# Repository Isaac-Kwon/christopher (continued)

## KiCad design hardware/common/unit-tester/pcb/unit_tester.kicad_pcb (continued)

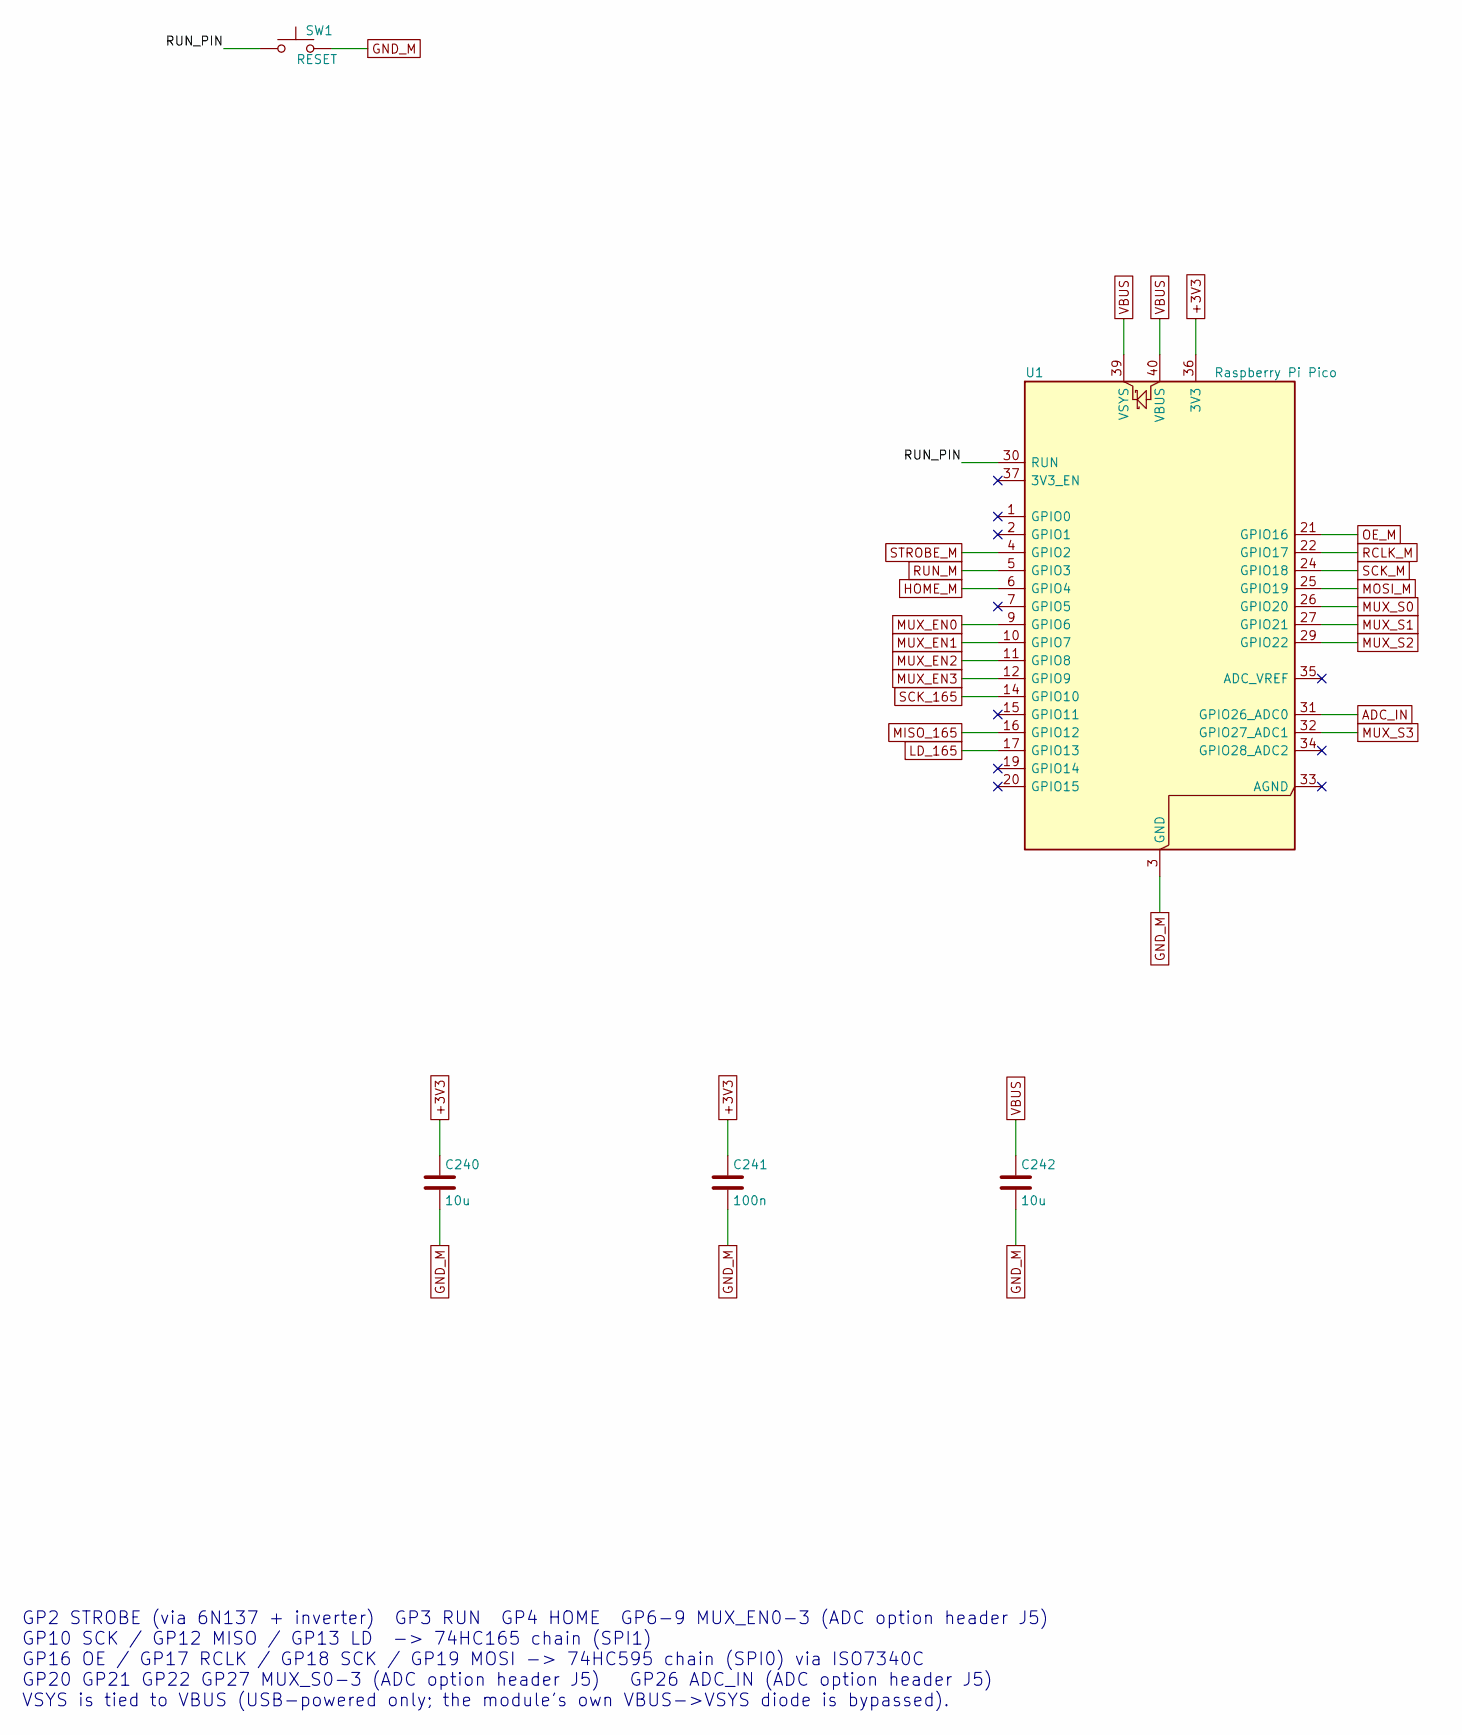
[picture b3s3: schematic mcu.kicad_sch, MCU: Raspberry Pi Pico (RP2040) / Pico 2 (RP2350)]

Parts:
C240, C242: 10u; C_0805_2012Metric
C241: 100n; C_0603_1608Metric
SW1: RESET; SW_SPST_PTS645Sx43SMTR92
U1: Raspberry Pi Pico; RaspberryPi_Pico_Common_THT

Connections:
+3V3: C240.1, C241.1, U1.36 (3V3); also elsewhere on the board
/MCU/RUN_PIN: SW1.1, U1.30 (RUN)
ADC_IN: U1.31 (GPIO26_ADC0); also elsewhere on the board
GND_M: C240.2, C241.2, C242.2, SW1.2, U1.3 (GND), U1.8 (GND), U1.13 (GND), U1.18 (GND), U1.23 (GND), U1.28 (GND), U1.38 (GND); also elsewhere on the board
HOME_M: U1.6 (GPIO4); also elsewhere on the board
LD_165: U1.17 (GPIO13); also elsewhere on the board
MISO_165: U1.16 (GPIO12); also elsewhere on the board
MOSI_M: U1.25 (GPIO19); also elsewhere on the board
MUX_EN0: U1.9 (GPIO6); also elsewhere on the board
MUX_EN1: U1.10 (GPIO7); also elsewhere on the board
MUX_EN2: U1.11 (GPIO8); also elsewhere on the board
MUX_EN3: U1.12 (GPIO9); also elsewhere on the board
MUX_S0: U1.26 (GPIO20); also elsewhere on the board
MUX_S1: U1.27 (GPIO21); also elsewhere on the board
MUX_S2: U1.29 (GPIO22); also elsewhere on the board
MUX_S3: U1.32 (GPIO27_ADC1); also elsewhere on the board
OE_M: U1.21 (GPIO16); also elsewhere on the board
RCLK_M: U1.22 (GPIO17); also elsewhere on the board
RUN_M: U1.5 (GPIO3); also elsewhere on the board
SCK_165: U1.14 (GPIO10); also elsewhere on the board
SCK_M: U1.24 (GPIO18); also elsewhere on the board
STROBE_M: U1.4 (GPIO2); also elsewhere on the board
VBUS: C242.1, U1.39 (VSYS), U1.40 (VBUS)

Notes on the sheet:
GP2 STROBE (via 6N137 + inverter) GP3 RUN GP4 HOME GP6-9 MUX_EN0-3 (ADC option header J5) GP10 SCK / GP12 MISO / GP13 LD -> 74HC165 chain (SPI1) GP16 OE / GP17 RCLK / GP18 SCK / GP19 MOSI -> 74HC595 chain (SPI0) via ISO7340C GP20 GP21 GP22 GP27 MUX_S0-3 (ADC option header J5) GP26 ADC_IN (ADC optio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

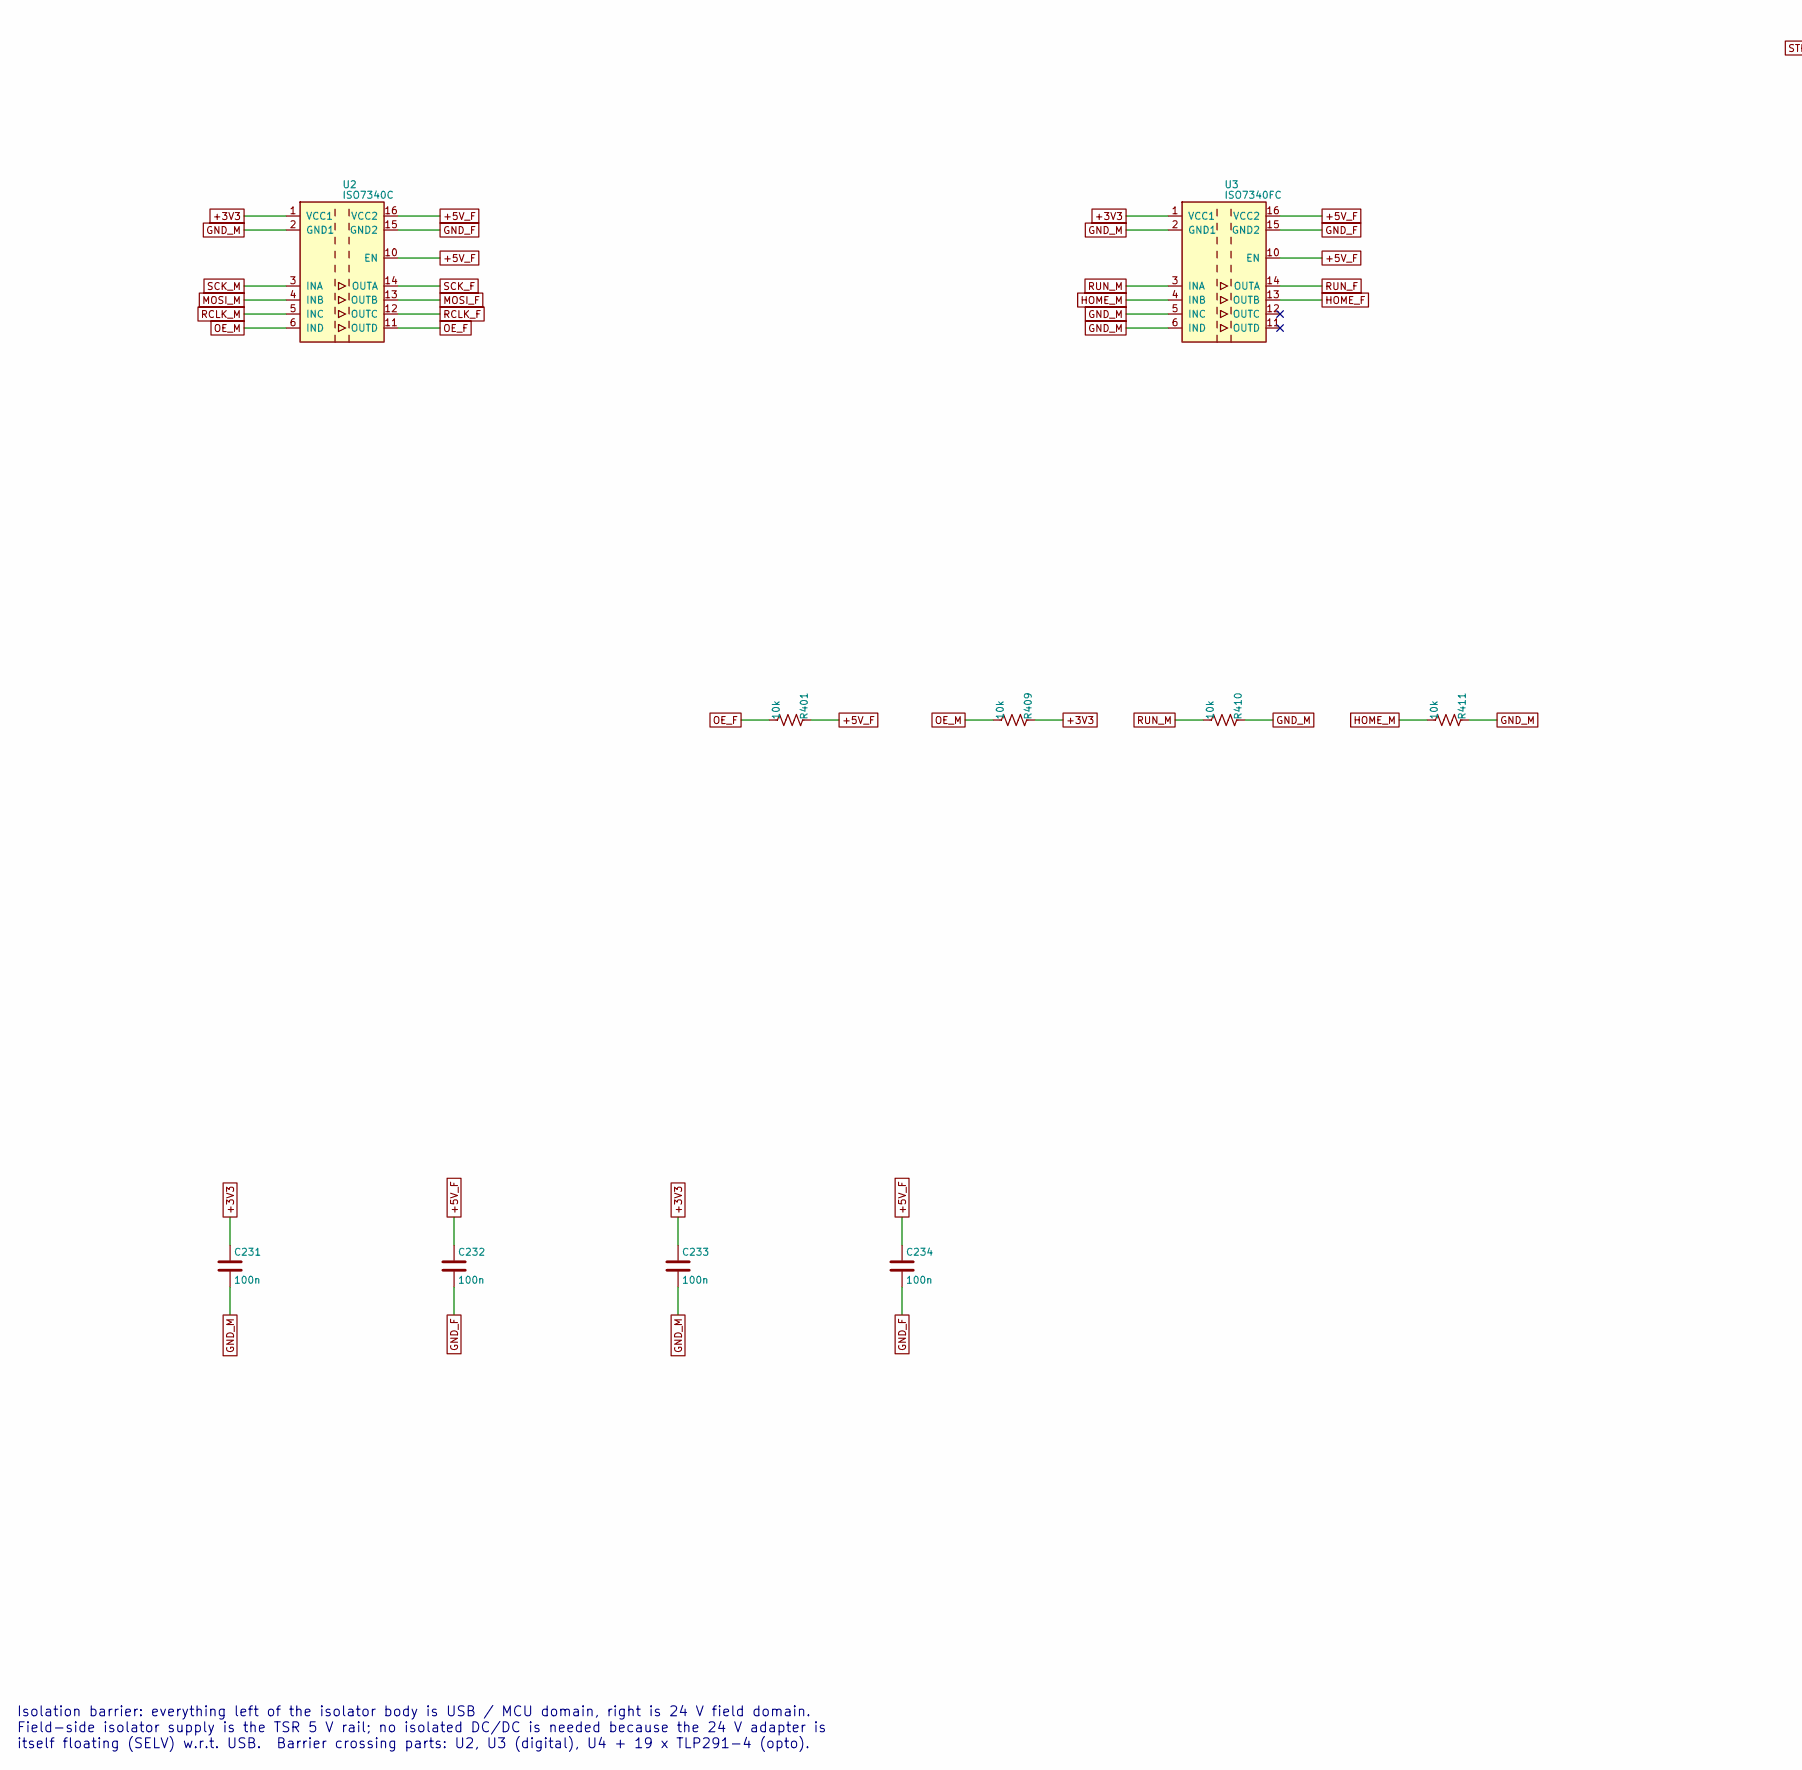
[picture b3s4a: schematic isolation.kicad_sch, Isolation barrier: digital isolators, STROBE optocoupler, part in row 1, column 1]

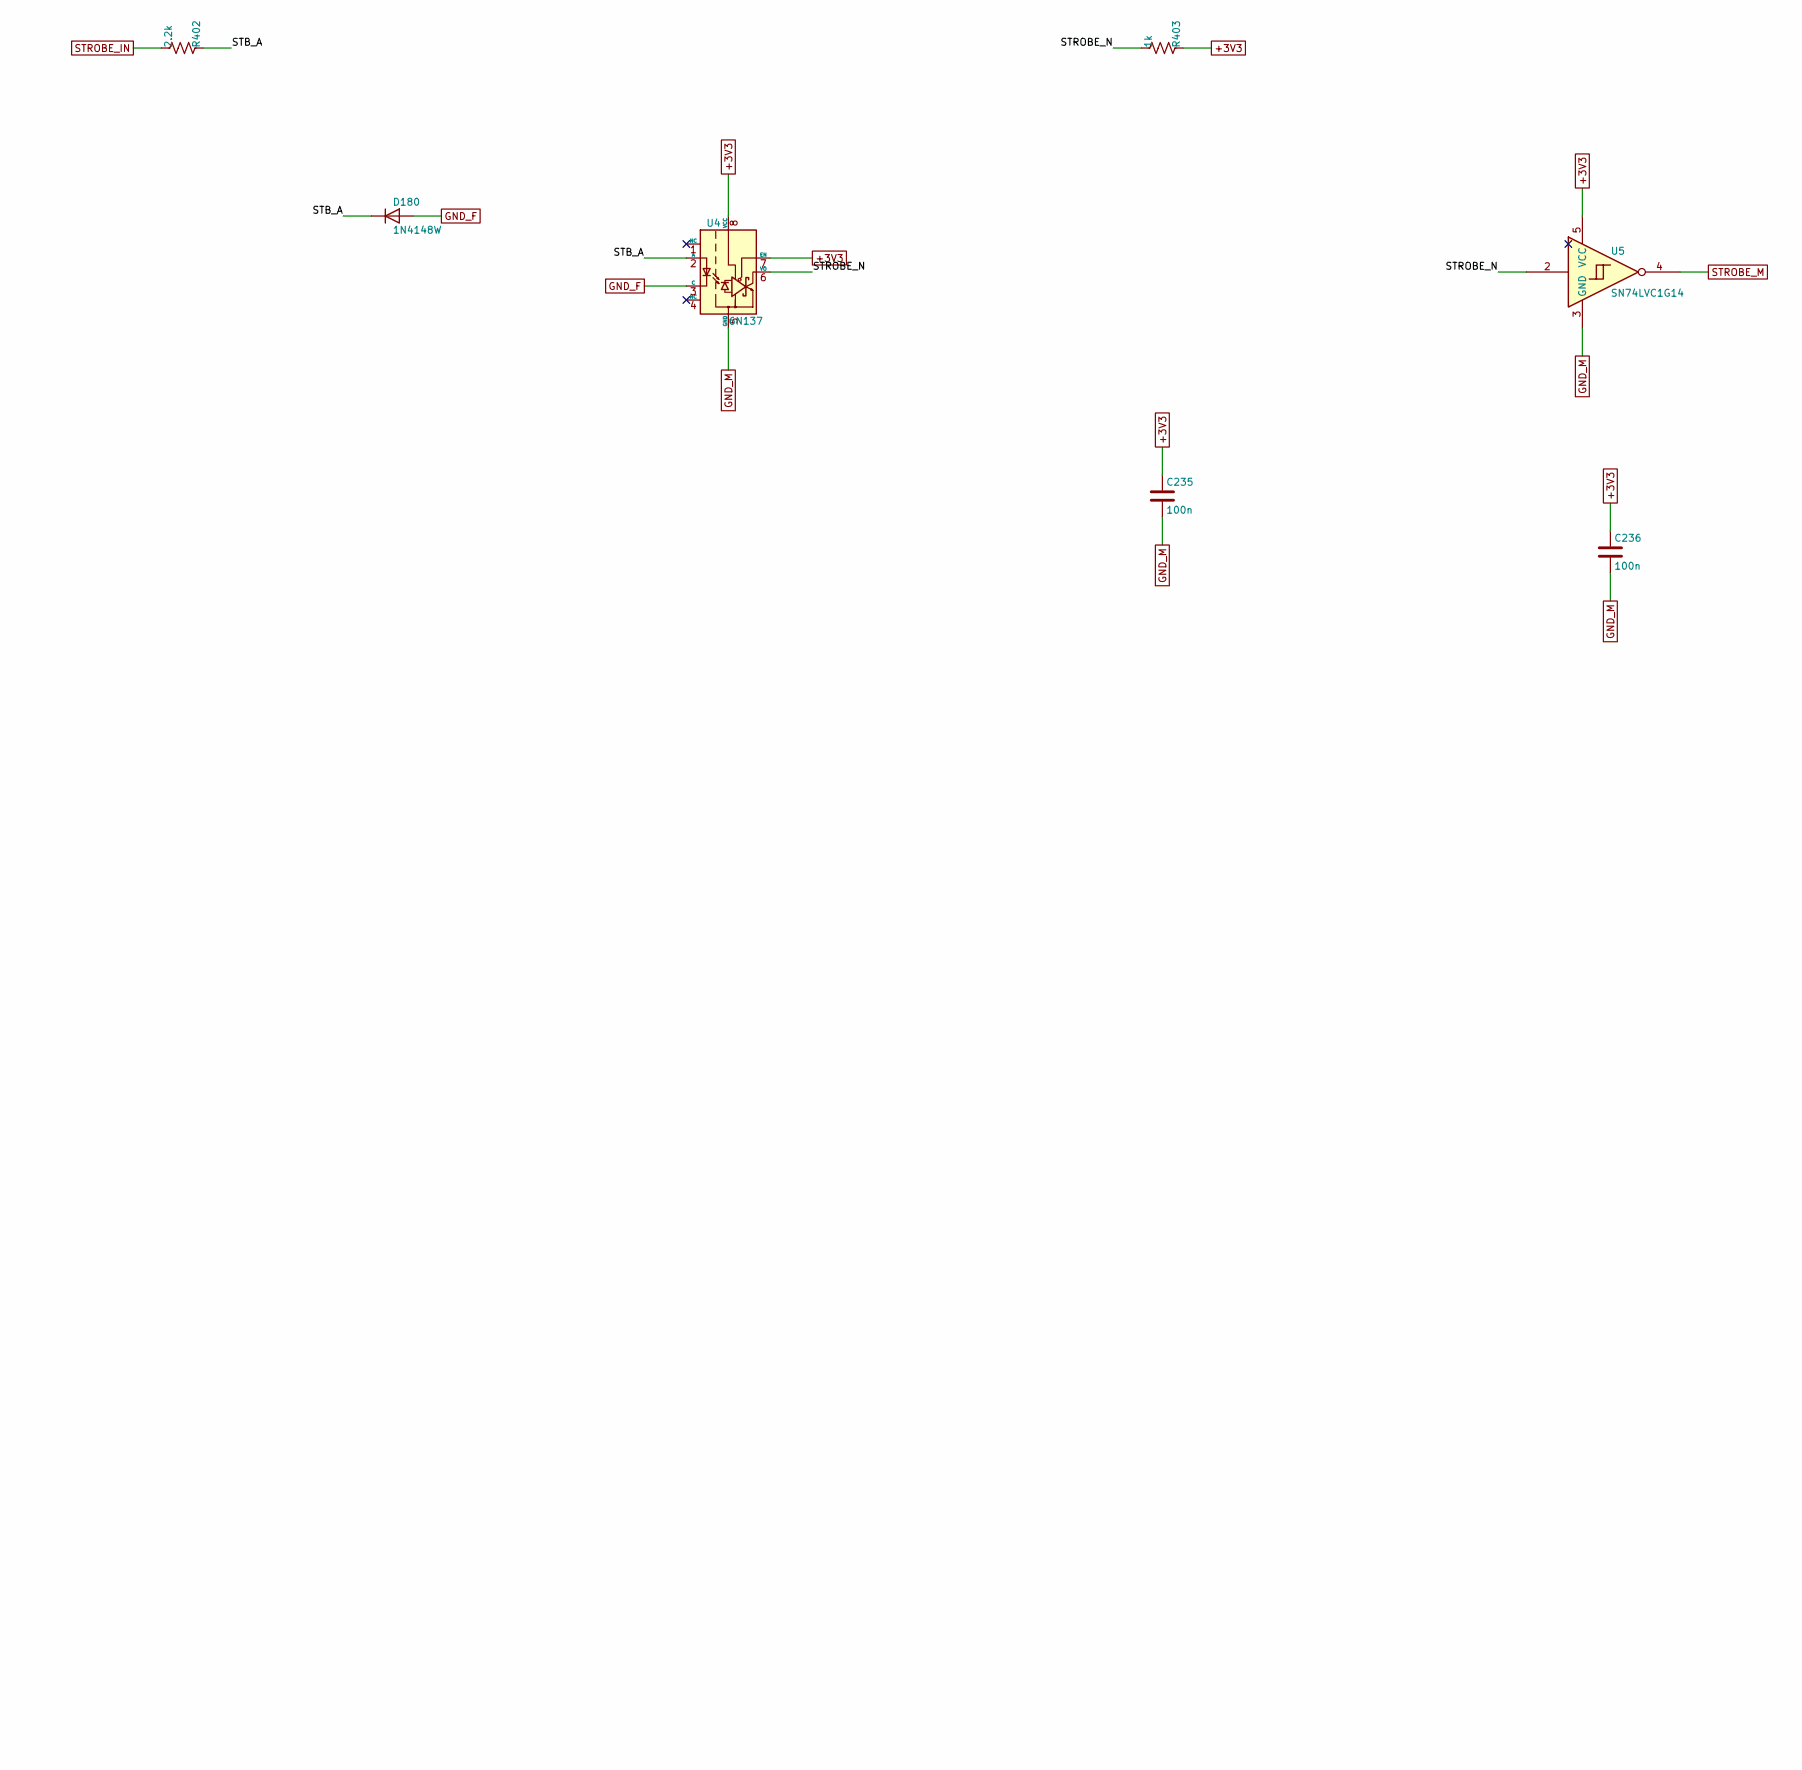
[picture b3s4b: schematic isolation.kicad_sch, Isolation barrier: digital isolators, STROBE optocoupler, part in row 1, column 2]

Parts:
C231, C232, C233, C234, C235, C236: 100n; C_0603_1608Metric
D180: 1N4148W; D_SOD-123
R401, R409, R410, R411: 10k; R_0603_1608Metric
R402: 2.2k; R_0603_1608Metric
R403: 1k; R_0603_1608Metric
U2: ISO7340C; SOIC-16W_7.5x10.3mm_P1.27mm
U3: ISO7340FC; SOIC-16W_7.5x10.3mm_P1.27mm
U4: 6N137; DIP-8_W7.62mm
U5: SN74LVC1G14; SOT-23-5

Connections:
+3V3: C231.1, C233.1, C235.1, C236.1, R403.2, R409.2, U2.1 (VCC1), U3.1 (VCC1), U4.7 (EN), U4.8 (VCC), U5.5 (VCC); also elsewhere on the board
+5V_F: C232.1, C234.1, R401.2, U2.10 (EN), U2.16 (VCC2), U3.10 (EN), U3.16 (VCC2); also elsewhere on the board
/ISOLATION/STB_A: D180.1 (K), R402.2, U4.2 (A)
/ISOLATION/STROBE_N: R403.1, U4.6 (VO), U5.2
GND_F: C232.2, C234.2, D180.2 (A), U2.9 (GND2), U2.15 (GND2), U3.9 (GND2), U3.15 (GND2), U4.3 (C); also elsewhere on the board
GND_M: C231.2, C233.2, C235.2, C236.2, R410.2, R411.2, U2.2 (GND1), U2.8 (GND1), U3.2 (GND1), U3.5 (INC), U3.6 (IND), U3.8 (GND1), U4.5 (GND), U5.3 (GND); also elsewhere on the board
HOME_F: U3.13 (OUTB); also elsewhere on the board
HOME_M: R411.1, U3.4 (INB); also elsewhere on the board
MOSI_F: U2.13 (OUTB); also elsewhere on the board
MOSI_M: U2.4 (INB); also elsewhere on the board
OE_F: R401.1, U2.11 (OUTD); also elsewhere on the board
OE_M: R409.1, U2.6 (IND); also elsewhere on the board
RCLK_F: U2.12 (OUTC); also elsewhere on the board
RCLK_M: U2.5 (INC); also elsewhere on the board
RUN_F: U3.14 (OUTA); also elsewhere on the board
RUN_M: R410.1, U3.3 (INA); also elsewhere on the board
SCK_F: U2.14 (OUTA); also elsewhere on the board
SCK_M: U2.3 (INA); also elsewhere on the board
STROBE_IN: R402.1; also elsewhere on the board
STROBE_M: U5.4; also elsewhere on the board

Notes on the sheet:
Isolation barrier: everything left of the isolator body is USB / MCU domain, right is 24 V field domain. Field-side isolator supply is the TSR 5 V rail; no isolated DC/DC is needed because the 24 V adapter is itself floating (SELV) w.r.t. USB. Barrier crossing parts: U2, U3 (digital), U4 + 19 x TLP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

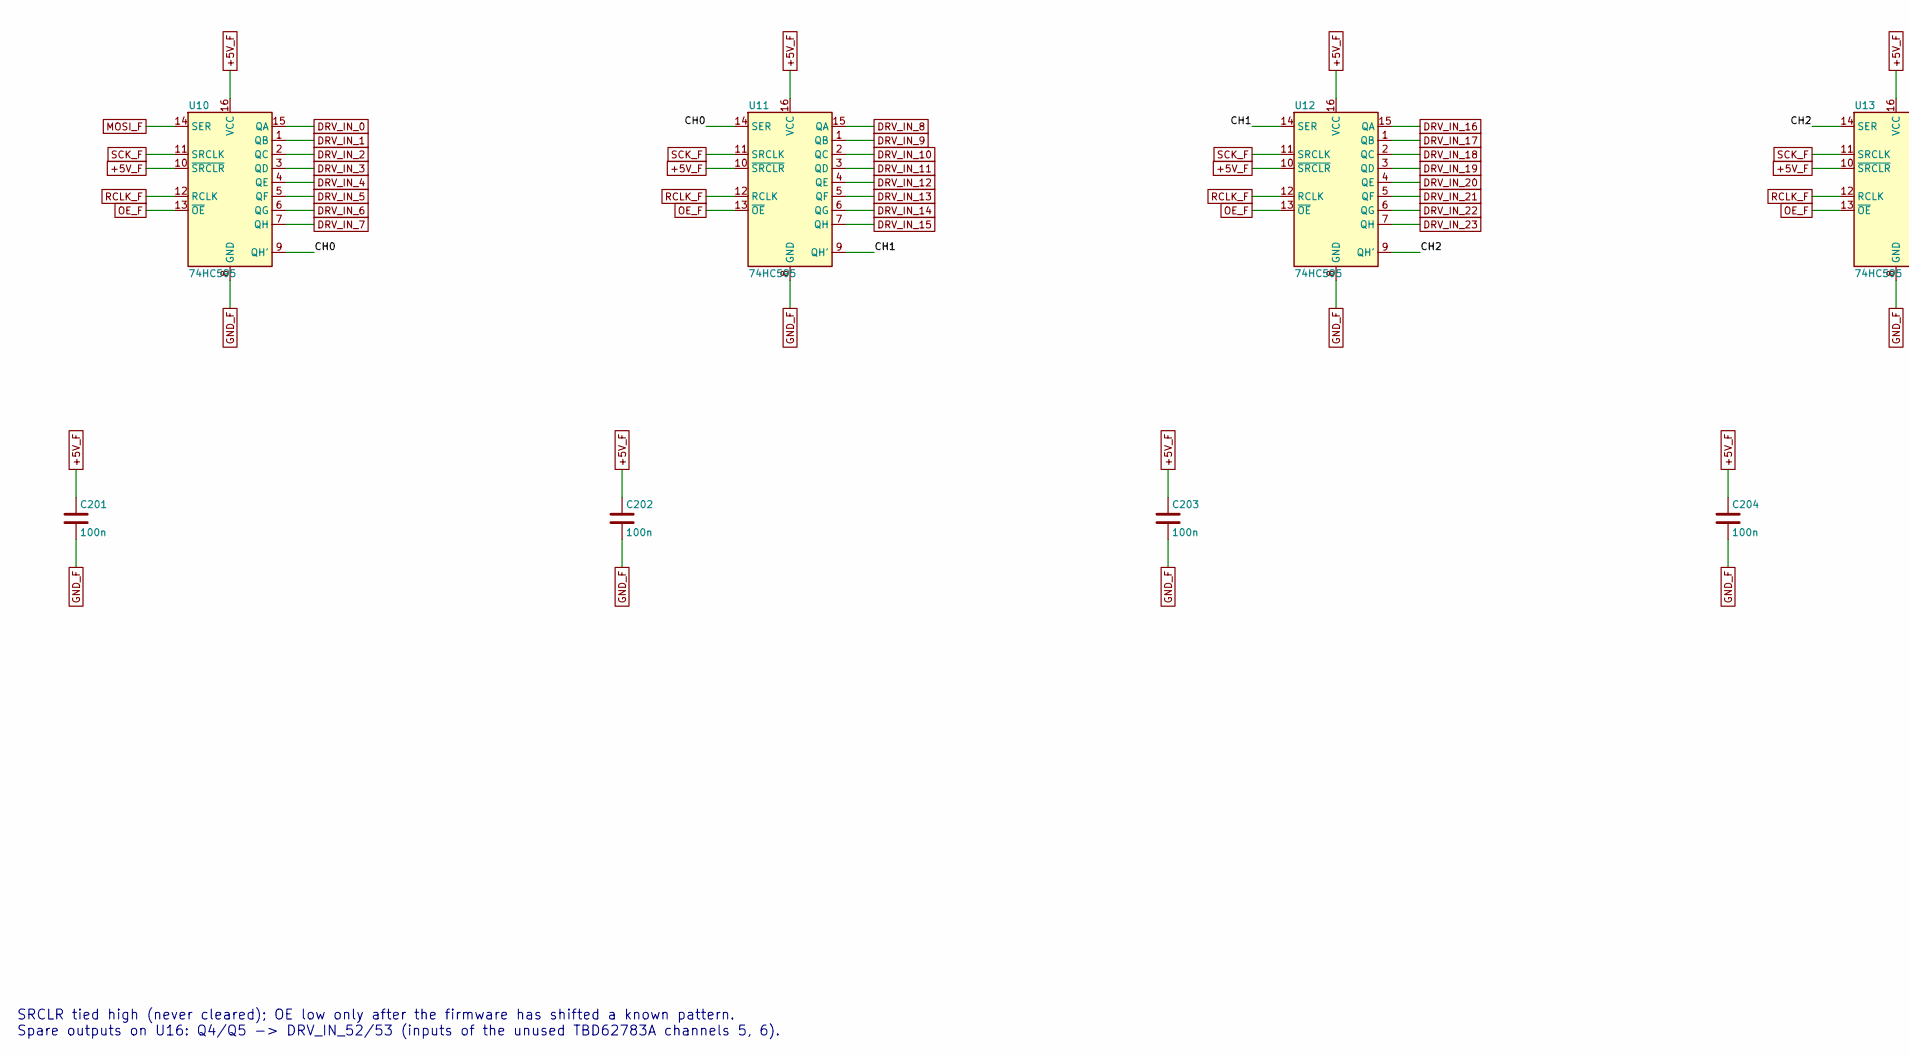
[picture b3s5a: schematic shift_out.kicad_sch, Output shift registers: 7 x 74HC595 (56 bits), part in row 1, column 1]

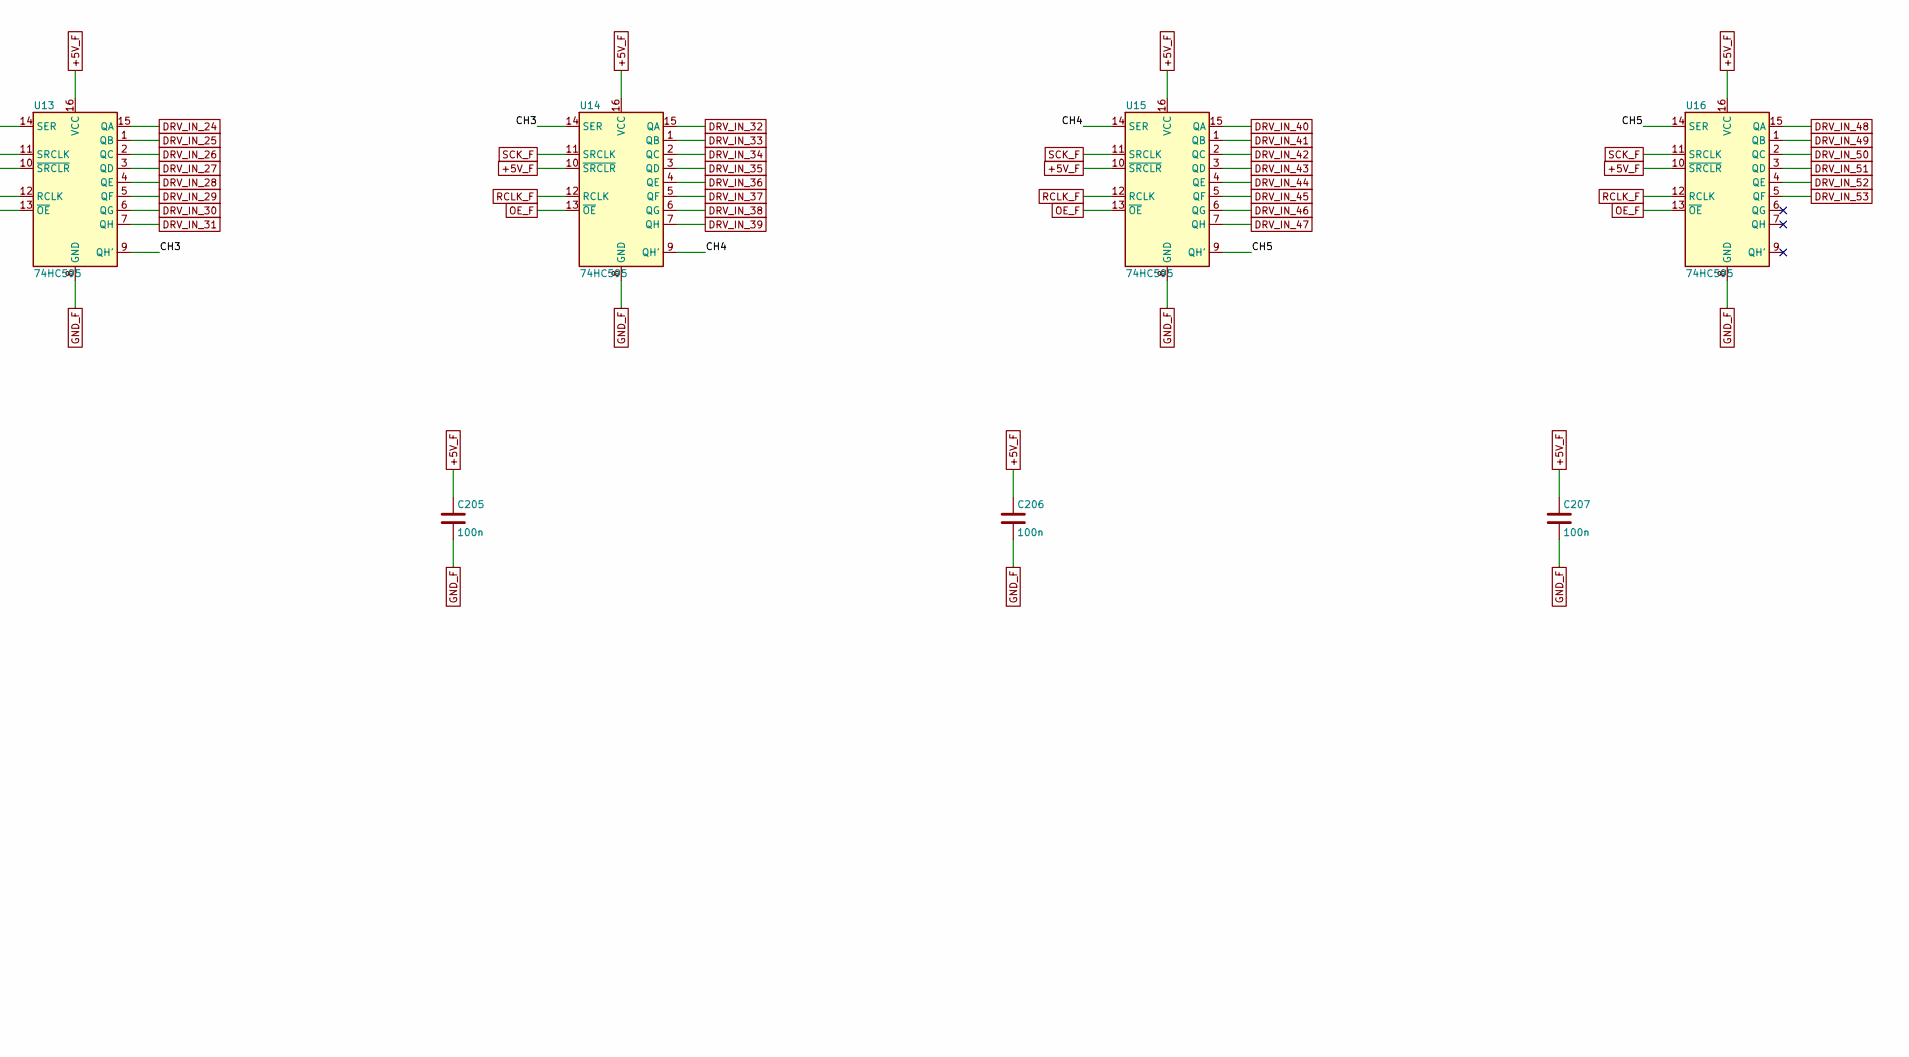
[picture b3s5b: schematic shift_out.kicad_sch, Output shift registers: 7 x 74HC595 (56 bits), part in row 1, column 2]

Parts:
C201, C202, C203, C204, C205, C206, C207: 100n; C_0603_1608Metric
U10, U11, U12, U13, U14, U15, U16: 74HC595; SOIC-16_3.9x9.9mm_P1.27mm

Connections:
+5V_F: C201.1, C202.1, C203.1, C204.1, C205.1, C206.1, C207.1, U10.10 (~SRCLR), U10.16 (VCC), U11.10 (~SRCLR), U11.16 (VCC), U12.10 (~SRCLR), U12.16 (VCC), U13.10 (~SRCLR), U13.16 (VCC), U14.10 (~SRCLR), U14.16 (VCC), U15.10 (~SRCLR), U15.16 (VCC), U16.10 (~SRCLR), U16.16 (VCC); also elsewhere on the board
/SHIFT_OUT/CH0: U10.9 (QH'), U11.14 (SER)
/SHIFT_OUT/CH1: U11.9 (QH'), U12.14 (SER)
/SHIFT_OUT/CH2: U12.9 (QH'), U13.14 (SER)
/SHIFT_OUT/CH3: U13.9 (QH'), U14.14 (SER)
/SHIFT_OUT/CH4: U14.9 (QH'), U15.14 (SER)
/SHIFT_OUT/CH5: U15.9 (QH'), U16.14 (SER)
DRV_IN_0: U10.15 (QA); also elsewhere on the board
DRV_IN_1: U10.1 (QB); also elsewhere on the board
DRV_IN_2: U10.2 (QC); also elsewhere on the board
DRV_IN_3: U10.3 (QD); also elsewhere on the board
DRV_IN_4: U10.4 (QE); also elsewhere on the board
DRV_IN_5: U10.5 (QF); also elsewhere on the board
DRV_IN_6: U10.6 (QG); also elsewhere on the board
DRV_IN_7: U10.7 (QH); also elsewhere on the board
DRV_IN_8: U11.15 (QA); also elsewhere on the board
DRV_IN_9: U11.1 (QB); also elsewhere on the board
DRV_IN_10: U11.2 (QC); also elsewhere on the board
DRV_IN_11: U11.3 (QD); also elsewhere on the board
DRV_IN_12: U11.4 (QE); also elsewhere on the board
DRV_IN_13: U11.5 (QF); also elsewhere on the board
DRV_IN_14: U11.6 (QG); also elsewhere on the board
DRV_IN_15: U11.7 (QH); also elsewhere on the board
DRV_IN_16: U12.15 (QA); also elsewhere on the board
DRV_IN_17: U12.1 (QB); also elsewhere on the board
DRV_IN_18: U12.2 (QC); also elsewhere on the board
DRV_IN_19: U12.3 (QD); also elsewhere on the board
DRV_IN_20: U12.4 (QE); also elsewhere on the board
DRV_IN_21: U12.5 (QF); also elsewhere on the board
DRV_IN_22: U12.6 (QG); also elsewhere on the board
DRV_IN_23: U12.7 (QH); also elsewhere on the board
DRV_IN_24: U13.15 (QA); also elsewhere on the board
DRV_IN_25: U13.1 (QB); also elsewhere on the board
DRV_IN_26: U13.2 (QC); also elsewhere on the board
DRV_IN_27: U13.3 (QD); also elsewhere on the board
DRV_IN_28: U13.4 (QE); also elsewhere on the board
DRV_IN_29: U13.5 (QF); also elsewhere on the board
DRV_IN_30: U13.6 (QG); also elsewhere on the board
DRV_IN_31: U13.7 (QH); also elsewhere on the board
DRV_IN_32: U14.15 (QA); also elsewhere on the board
DRV_IN_33: U14.1 (QB); also elsewhere on the board
DRV_IN_34: U14.2 (QC); also elsewhere on the board
DRV_IN_35: U14.3 (QD); also elsewhere on the board
DRV_IN_36: U14.4 (QE); also elsewhere on the board
DRV_IN_37: U14.5 (QF); also elsewhere on the board
DRV_IN_38: U14.6 (QG); also elsewhere on the board
DRV_IN_39: U14.7 (QH); also elsewhere on the board
DRV_IN_40: U15.15 (QA); also elsewhere on the board
DRV_IN_41: U15.1 (QB); also elsewhere on the board
DRV_IN_42: U15.2 (QC); also elsewhere on the board
DRV_IN_43: U15.3 (QD); also elsewhere on the board
DRV_IN_44: U15.4 (QE); also elsewhere on the board
DRV_IN_45: U15.5 (QF); also elsewhere on the board
DRV_IN_46: U15.6 (QG); also elsewhere on the board
DRV_IN_47: U15.7 (QH); also elsewhere on the board
DRV_IN_48: U16.15 (QA); also elsewhere on the board
DRV_IN_49: U16.1 (QB); also elsewhere on the board
DRV_IN_50: U16.2 (QC); also elsewhere on the board
DRV_IN_51: U16.3 (QD); also elsewhere on the board
DRV_IN_52: U16.4 (QE); also elsewhere on the board
DRV_IN_53: U16.5 (QF); also elsewhere on the board
GND_F: C201.2, C202.2, C203.2, C204.2, C205.2, C206.2, C207.2, U10.8 (GND), U11.8 (GND), U12.8 (GND), U13.8 (GND), U14.8 (GND), U15.8 (GND), U16.8 (GND); also elsewhere on the board
MOSI_F: U10.14 (SER); also elsewhere on the board
OE_F: U10.13 (~OE), U11.13 (~OE), U12.13 (~OE), U13.13 (~OE), U14.13 (~OE), U15.13 (~OE), U16.13 (~OE); also elsewhere on the board
RCLK_F: U10.12 (RCLK), U11.12 (RCLK), U12.12 (RCLK), U13.12 (RCLK), U14.12 (RCLK), U15.12 (RCLK), U16.12 (RCLK); also elsewhere on the board
SCK_F: U10.11 (SRCLK), U11.11 (SRCLK), U12.11 (SRCLK), U13.11 (SRCLK), U14.11 (SRCLK), U15.11 (SRCLK), U16.11 (SRCLK); also elsewhere on the board

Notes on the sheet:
SRCLR tied high (never cleared); OE low only after the firmware has shifted a known pattern. Spare outputs on U16: Q4/Q5 -> DRV_IN_52/53 (inputs of the unused TBD62783A channels 5, 6).
